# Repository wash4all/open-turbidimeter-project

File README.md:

# The Open Turbidimeter Project

## Contents
- [Background](#background)
- [What is "Turbidity"?](#what-is-turbidity)
- [Measuring Turbidity](#measuring-turbidity)
- [Goals for the Turbidimeter](#goals-for-the-turbidimeter)
- [Connectivity](#connectivity)
- [Development and Dependencies](#development-and-dependencies)
- [Licensing](#licensing)
- [Funding Sources](#funding-sources)
- [Contact](#contact)

## Background

The high cost of equipment to monitor water quality often puts valuable health tools out of reach for many communities in developing countries. Consequently, millions of people are exposed to health risks that could me mitigated if solutions were available at a price point they can afford. **The goal of our project is to create a low-cost device to measure the turbidity of a water supply.**

## What Is "Turbidity"?

Turbidity refers to the dirtiness or cloudiness of a water sample, and an internationally recognized criterion for assessing drinking water quality because the colloidal particles in turbid water may harbor pathogens, chemically reduce oxidizing disinfectants, and hinder attempts to disinfect water with ultraviolet radiation. Technicians at water treatment plants regularly measure water turbidity before and after treatment. It’s a legal requirement in many countries, and one indicator of whether treated water is safe for human consumption. The unaided eye can distinguish cloudy water from clear water, but even visibly clear samples of water can be dangerous.

## Measuring Turbidity

The quantification of turbidity is complicated by the fact that the goal is to obtain an aggregate quasi-concentration of *all* the different types of particles present in the water. This is different than, say measuring the concentration of a *specific* chemical by adding known quantities of reagents and measuring the mass of the resulting precipitate.

A turbidimeter is an optical instrument that assesses turbidity by measuring the scattering of light passing through a water sample. The general principle is that the more particles are floating around in the water, the more light will be scattered as it passes from on one side of a sample to the other. In its simplest form, a turbidimeter is just a light source and a photosensor arranged perpendicular to each other around a water sample. More complicated setups using multiple sensors and/or light sources extend the detection limit and accuracy of the device. Some possible layouts are shown below.

*Source:* [turbidimeter-designs.png](turbidimeter-designs.png)

Turbidity is most commonly quantified by the Nephelometric Turbidity Unit (NTU)**\***. The NTU scale is defined by reference standards which are created by diluting approved compounds to concentrations designated by the [EPA][EPA Method 180.1] and [ISO][ISO 7027]. The primary standard for this scale is formazin, although other (safer) secondary standards have been approved. Note that these regulations have additional stipulations such as the measurement angle and wavelength of the light source. Looking over the standards themselves is *highly recommended.*

The human eye can detect turbidity levels down to roughly 5 or 10 NTU. Samples of water with turbidity lower than this will appear clear, but may still contain a concentration of colloidal particles sufficient to impair disinfection efforts and may carry a load of contaminants or pathogens sufficient to cause serious human illness. Current EPA regulations stipulate that conventionally treated surface water in the USA must be regularly sampled, that only 5% of samples in a given month may show turbidity greater than 0.3 NTU, and that no sample may show turbidity in excess of 1.0 NTU. Other countries employ different standards, and the World Health Organization (WHO) recommends that turbidity levels be less than 0.1 NTU prior to disinfection.

Handheld units capable of analyzing a single sample vial cost several hundred dollars; automated units capable of intermittently analyzing samples from flowing water can cost several thousand. Partly completed open-source turbidimeter projects can be found online, apparently abandoned.

**\*** Nephelometry is the term given to the side-scatter method of measuring turbidity described above

[EPA Method 180.1]: (http://water.epa.gov/scitech/methods/cwa/bioindicators/upload/2007_07_10_methods_method_180_1.pdf)
[ISO 7027]: http://www.iso.org/iso/catalogue_detail.htm?csnumber=30123

## Goals for the Turbidimeter

1.  Costs less than $100 when economies of scale are applied to production
2.  Reads samples with an accuracy of:
    1.  0.05 NTU from 0-5 NTU
    2.  0.2 NTU from 5-20 NTU
    3.  5% from 20-1000 NTU
3.  Can be operated manually or in automated sampling mode
4.  Has wireless data transmission capability
5.  Uses a replaceable battery pack

An open-source turbidimeter fulfilling the design goals listed above will not quite meet the strict technical requirements of the EPA, but will nonetheless provide a huge improvement over the status-quo of rural and small-scale water treatment monitoring, at a realistic cost.

## Connectivity

The intent is for these devices to be deployed at rivers, wells, and treatment plants in possibly very remote areas that are visited infrequently by engineers and regulators from more urban areas. For this reason, the device will be integrated with a remote data-acquisition system to enable record keeping, troubleshooting, and real-time observation of water quality. We are exploring a few different ways of getting data off the device wirelessly.

**Bluetooth** ```tested``` ```firmware support```
Include a low-power Bluetooth module that sends data to a linked Android cellphone, which uses its data plan and SMS to sync to a remote server. The problem with this is that the cost of a smartphone doubles or triples the cost of the device. The phone itself is also subject to damage or theft, which cripples the data connection. The additional processing power and memory afforded by a smartphone, on the other hand, are attractive features.

**GSM Modem** ```tested``` ```firmware support```
Integrate a GSM modem (the core piece of technology used by mobile phones) into the turbidimeter itself to provide wireless connectivity. This is a less expensive approach, but has issues with reliability and increases power consumption *quite a bit*. We also want to encourage DIYers to build their own units, and prototyping GSM modules like the one sold by Arduino are still not cheap. Therefore we want to make sure that the turbidimeter can still be used without wireless capability if we go with this approach.

**Direct Connection to Mobile Phone** ```not tested``` ```no firmware support```
Connect the turbidimeter to an arbitrary mobile phone using a wired connection. This requires the hardware to support the connection (most likely a USB host adapter), but in theory any GSM-compliant phone would be controllable using it. Here's an example of an [Arduino-controlled Motorola Razr](https://www.circuitsathome.com/mcu/programming/interfacing-arduino-to-a-cellular-phone).

## Development and Dependencies

In the prototyping stage, most of the development is done using rapid prototyping tools like Arduino and 3D printed parts. We expect to transition off these tools soon as we finish designing custom components, although it will always be possible to build your own turbimeter by printing the parts and assembling the necessary circuitry.

A list of software and hardware dependencies is maintained in the file [Dependencies.md](Dependencies.md). We try to use all open-source design tools, although we are stuck with a few non-free packages at the moment. For these cases, we export to open formats (such as STL, STEP, and BRD).

Issue tracking, package releases, and the like are managed through GitHub, which is most likely where you are reading this anyways. To download the revision-controlled repository with all the latest code, use ```git clone https://github.com/wash4all/open-turbidimeter-project.git```. Alternately you can browse the [releases][] for a stable set of files that are known to work.

[releases]: https://github.com/wash4all/open-turbidimeter-project/releases

## Licensing

The software and documentation for the project are covered by the [GNU General Public License][gpl] and [Creative Commons ShareAlike-Attribution][cc] licenses, respectively.

[gpl]: https://www.gnu.org/copyleft/gpl.html
[cc]: https://creativecommons.org/licenses/by-sa/4.0/

## Funding Sources

The Open Turbidimeter Project has been funded in part by EPA Grant Number [SU835517][grant]: "Smart" Turbidimeters for Remote Monitoring of Water Quality.

[grant]: http://cfpub.epa.gov/ncer_abstracts/index.cfm/fuseaction/display.abstractDetail/abstract/10094/report/0

## Contact

Development of the Open Turbidimeter Project is facilitated by [WASH for All][], an organization working for universal access to clean drinking water and sanitation by developing innovative and cost-effective tools.

Contact [Chris][] or [Alex][] if you'd like to get involved with WASH for All or if you have questions about the project or the organization.

[WASH for All]: http://wash4all.org
[Chris]: mailto:iamchriskelley@gmail.com
[Alex]: mailto:amk283@cornell.edu

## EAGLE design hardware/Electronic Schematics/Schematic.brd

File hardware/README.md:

# Construction and Usage of the Turbidimeter

## Introduction

The sections below detail the necessary parts and tools, wiring, assembly, and microcontroller programming to get up and running with the Open Turbidimeter Project. You are encouraged to contact the team members with any questions about the construction, operation, or expansion of this device.

## Components List

All components of the open-source turbidimeter are indicated in the [Parts List](Parts List.tsv), along with potential
distributors. Indicated costs are for individual pieces and do not include shipping and handling or taxes.

## Structural Components

The open-source turbidimeter case consists of four different parts: (1) bottom, which includes ports for button and on/off switch; (2) cuvette holder, which houses the sensor and light source and holds the glass cuvette during device operation; (3) top, which has openings for the seven-segment LED display and the top of the cuvette holder; and (4) battery lid, which slides out from the case assembled case top and bottom to expose the battery holder. Electronic files of these objects (in STL format) are available in the [3D Design Files](3D Design Files/) folder. Note that any container that provides good shielding from incidental light may suffice for the larger portion of the case (e.g. a nested pair of cardboard boxes).

Link: [Assembly.png](3D Design Files/Assembly.png)

_**Fig 1** Image of the open-source turbidimeter with major dimensions given. The four smaller images (left to right) are the case lid (top left), the case base (bottom left), the battery lid (top right), and the cuvette holder (bottom right). All dimensions are in millimeters._

## Tools

A utility knife, soldering iron, and solder are required for assembly of the open-source turbidimeter, and safety goggles are recommended. To replicate the printed four-part case, one must have access to a 3D-printer with black ABS filament. The microprocessor can be programmed via a USB-to-Serial adapter (Mouser carries one [#A000059] for $14.95) or with an Arduino (as described in this [tutorial](http://arduino.cc/en/Tutorial/ArduinoToBreadboard). Electrical tape is very helpful (for grouping wires
together), as are a pair of wire strippers.

## Turbidimeter Breadboard and Schematic

The microprocessor and connected components of the open-source turbidimeter are depicted below in Fritzing (Figure S2) and EAGLE formats (Figure S3). Figure S2 depicts what the device looks like internally, while Figure S3 is a more formal schematic.

Link: [Fritzing Diagram](Electronic Schematics/Fritzing Diagram.png)
	
_**Fig 2** Depiction of the internal components of the open-source turbidimeter (components labels cross-referenced in the parts list and Figure S3)_

Link: [Circuit Schematic](Electronic Schematics/Schematic.png)

_**Fig 3** Schematic of the circuit board for the open-source turbidimeter (components labels cross-referenced in Table S1 and Figure S2)._

## Basic Assembly Instructions

1.  Gather the components listed in Section 1, and the tools listed in Section 3.
2.  Print the parts described in Section 2 (or devise your own light-shielding case).
3.  Wire together the internal components of the open-source turbidimeter according to Figures 2 and 3. Here are some key points:
    1.  It's hard to see some connections of the circuit, such as the wiring of the voltage regulator (VR1), on Figure 2. The Arduino website has a well-illustrated tutorial on wiring the ATMega328P microprocessor (http://arduino.cc/en/Main/Standalone) that the reader may find useful.
    2.  The semi-circles on the microprocessor (IC1) and shift register (IC2) indicate orientation of these components. It is vital that chips are aligned properly using these guides. Wiring them in the opposite orientation will destroy the chips once voltage is applied! Please note that the semi-circle on the TSL230R sensor in Figure 2 is merely a visual aid, and is not present on the actual chip.
    3.  The pins of the seven-segment display are diagrammed by the distributor Electrodragon (http://www.electrodragon.com/w/index.php?title=7-Segment_Display). The linked document maps pin placement to function and representation in Figure 3 (e.g., the bottom left pin on the seven-segment display is pin 12, which maps to segment E of the display, which connects to port QE on the shift register).
    4.  Resistors R2 and R3 combine to form a voltage divider, which is used to measure the voltage provided by the batteries. To achieve useful results, use resistors with tolerance of 1% or less. Tolerance levels of 5% are suitable for the other resistors in the device.
    5.  The internal components list generally should be followed closely, however the power switch (S1) and button (S2) can easily be changed to suit the builder's aesthetic.
    6.  As always, exercise caution. Do not attempt construction of any electrical device without knowledge of proper technique and safety.

## Programming

The files included in the ```software``` folder of the project need to be compiled and uploaded to the microcontroller to get the device working. Connect the device to a computer using a properly wired [USB-to-Serial adapter](http://arduino.cc/en/Main/USBSerial) (this requires the use of an additional 100nf capacitor) or an [Arduino board](http://arduino.cc/en/Tutorial/ArduinoToBreadboard). Then install the [Arduino programming environment](http://arduino.cc/en/main/software). After followng the instructions in the sofware readme to install the necessary libraries, open the ```turbidimeter.ino``` program in the Arduino software and upload it to the microcontroller.

You're ready to go!

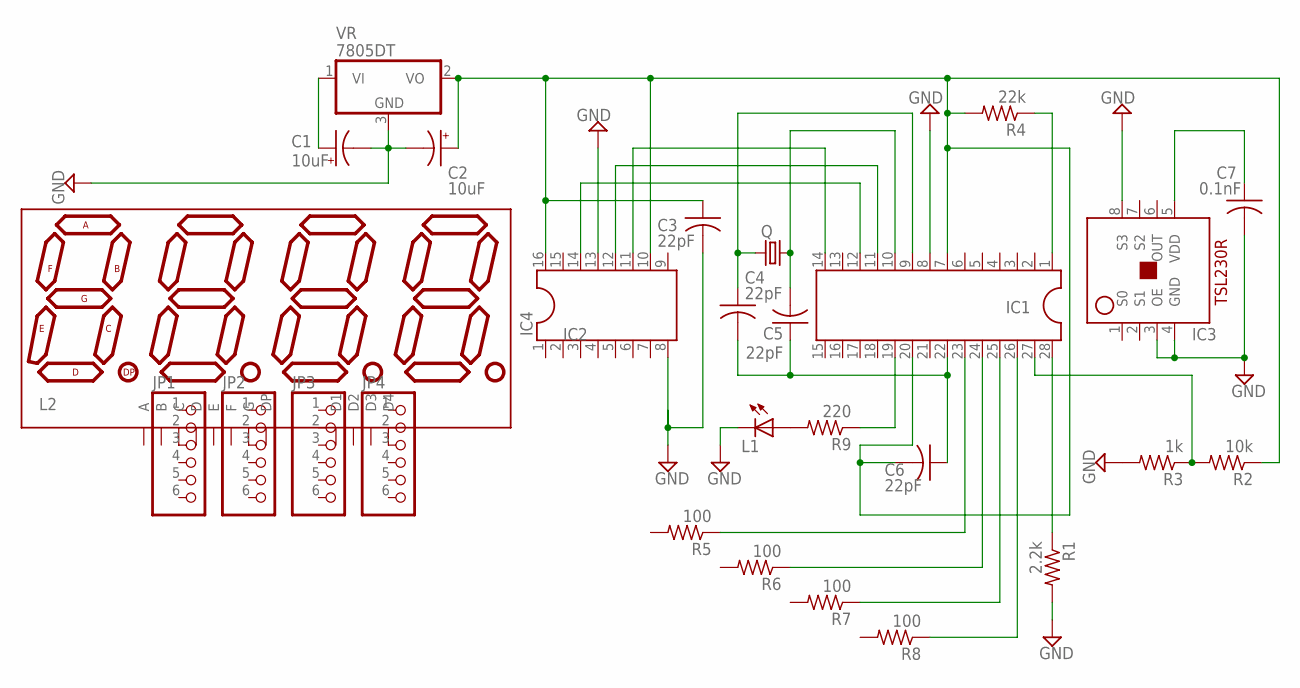
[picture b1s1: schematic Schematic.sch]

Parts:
C1, C2: 10uF; 140CLH-1010
C3, C4, C5, C6: 22pF; C025-024X044
C7: 0.1nF; C025-024X044
IC1: DIL28; DIL28-6
IC3: LIGHT_TO_FREQ_CONVERTER
IC4: DIL16
JP1, JP2, JP3, JP4: PINHD-1X6CLEAN; 1X06-CLEAN
L1: LEDIRL80A; IRL80A
Q: CRYSTALHC49S; HC49/S
R1: 2.2k; 0207/12
R2: 10k; 0207/12
R3: 1k; 0207/12
R4: 22k; 0207/12
R5, R6, R7, R8: 100; 0207/12
R9: 220; 0207/12
U$1: 7-SEGMENT-4DIGIT-COUNTERPTH; 7-SEGMENT-4DIGIT-COUNTER
VR: 7805DT; TO252

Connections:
GND: C1.-, C2.-, C3.2, C7.2, IC1.8, IC3.3 (OE), IC3.4 (GND), IC3.8 (S3), IC4.8, IC4.13, L1.K (C), R1.2, R3.2, VR.3 (GND)
unnamed: IC1.24, R6.1
unnamed: IC1.23, R5.1
unnamed: IC1.25, R7.1
unnamed: IC1.26, R8.1
unnamed: IC1.28, R1.1
unnamed: IC1.19, R9.1
unnamed: L1.A, R9.2
unnamed: IC1.11, IC4.12
unnamed: C4.2, C5.1, C6.1, IC1.22
unnamed: C1.+, VR.1 (VI)
unnamed: JP1.3, U$1.4 (C)
unnamed: IC1.12, IC4.14
unnamed: C4.1, IC1.9, Q.2
unnamed: C2.+, C3.1, C6.2, IC1.7, IC1.20, IC4.10, IC4.16, R2.1, R4.2, VR.2 (VO)
unnamed: IC1.1, R4.1
unnamed: IC1.14, IC4.11
unnamed: C7.1, IC3.5 (VDD)
unnamed: JP2.3, U$1.5 (G)
unnamed: JP4.3, U$1.6 (D4)
unnamed: IC1.27, R2.2, R3.1
unnamed: C5.2, IC1.10, Q.1

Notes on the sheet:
IC2
IC3

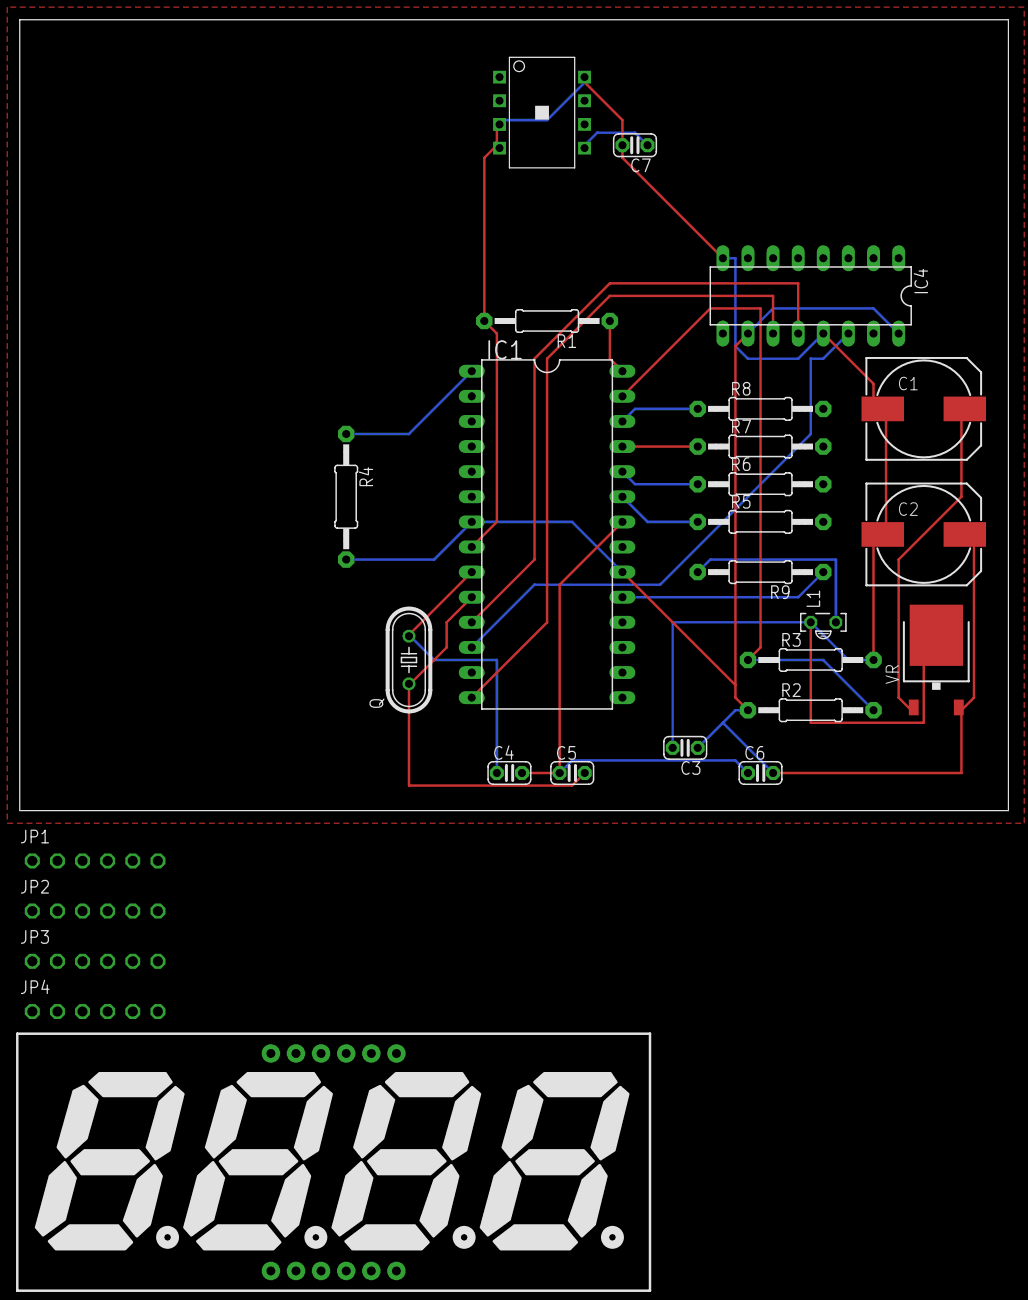
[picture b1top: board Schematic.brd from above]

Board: 2 copper layers, 100.0 x 80.0 mm, 27 parts (0 on the bottom side), 22 nets.

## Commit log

2013-07-03 first GitHub commit
2014-02-09 firmware for latest hardware
2014-02-10 Using CC-BY-SA 4.0 Int'l license
2014-02-10 Start adding SMS (text message) send/receive/parse functions.
    This commit breaks almost everything. Refer to the main branch ("master")
    for the latest stable code.
2014-02-10 bring linked libraries up to date
2014-02-10 Revert "bring linked libraries up to date"
    This reverts commit ad1d8b214ba15868f29ca10c1a533a00a7440cbc.
2014-02-10 bring firmware libraries up to date
2014-02-10 typo fix in license header
2014-02-11 Add parts list
2014-02-11 "Code style fixes"
2014-02-11 Update turbidimeter.ino
    changed variable definitions for voltage divider, and add GSM-related comments in several places
2014-02-11 resolve interrupt conflicts (bug #5)
2014-03-10 Create gsm_integration_code_update
    Not sure if I'm following protocol here properly, Alex. This is an updated version of the main INO file. Main changes are:
    -removed program control of the modem Rx pin (pin 3), which was hanging program flow
    -simplified the display functions, saving a lot of calculation (numbers are assigned to specific digits on the seven-segment only once, instead of each time they are flashed for POV)
    -correctly implemented the bit shift logic to allow easy swapout of common anode and cathode
    -put in a note on how to identify if a seven-segment display is common cathode or common anode
2014-03-14 SMS parsing update
2014-03-14 separate raw readings from NTU conversion
2014-03-14 function format fix
2014-03-14 fix annoying linewrap
2014-03-14 Delete gsm_integration_code_update
    changes absorbed into firmware sketch
2014-03-27 add circuit schematic source files
2014-03-27 add a bibtex file of relevant literature
2014-03-27 update software readme
2014-03-28 add assembly instructions and hardware files
2014-03-28 clear out old files
2014-03-28 fix documentation
2014-03-28 fix (?) markdown rendering issue
2014-03-28 update File Extensions guide and rename to Dependencies
2014-03-30 add calibration function
2014-03-31 implement inbound SMS parsing
2014-03-31 remove extra lines from calibration code
2014-03-31 split firmware into multiple files
2014-04-03 create hardware- and software-specific license files
2014-04-04 big update to documentation
2014-04-04 fix README table of contents
2014-04-04 really fix README table of contents
2014-04-04 declare funding sources
2014-04-08 resurrect serial-over-bluetooth capability
2014-04-10 elaborate on connectivity section of readme
2014-04-10 Add support status notice to connectivity options
2014-04-23 Update turbidimeter.ino
    correctly places Serial input in the program logic, and allows sample reading to be triggered either by Bluetooth or by button press.
2014-04-24 Update voltagemeter.ino
    adding temperature correction
2014-04-24 Fix bug that blocks change user command from being parsed
2016-10-04 minor edits
2016-10-04 fixed missing variable declaration

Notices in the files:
parts and their libraries:
SparkFun-Displays: Licensing: CC v3.0 Share-Alike You are welcome to use this library for commercial purposes.
